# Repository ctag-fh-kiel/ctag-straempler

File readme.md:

# **CTAG Strämpler**
This repository contains the firmware and the hardwaredesigns (CTAG and [Antumbra](http://www.antumbra.eu/)) of Strämpler.

!!**NEW**!! Strämpler firmware can now be built in the cloud using Github actions
!!**NEW**!! Strämpler can now run [CTAG TBD](https://github.com/ctag-fh-kiel/ctag-tbd) as alternative firmware! Enclosed in /bin folder!

## What it is:
- Half streamer, half sampler, therefore called Strämpler (close to German word of Strampler meaning romper suit).
- Allows streaming of large audio files from SD card (limit 2GB file size due to FAT32 used).
- A eurorack modular synth module with 22 HP width and an internet connection.
- A bridge to connect to [freesound.org](https://freesound.org), to play with samples within your modular synth setup.
- Allows tweaking of your sound just like you'd do with a sampler + *a modular synth*.
- Allows to parameter tweak and modulate sounds by control voltage (CV), employing a complex modulation matrix.

## Why it is:
- A group of audio enthusiasts enjoying coding and hardware making.
- The sexiness of sampling for sound design and synthesis.
- The (subjective) need to have more sampling modules in the eurorack modular synth domain.
- The (subjective) need to make eurorack more compatible with internet of things.
- Build a platform to learn, build and practise skills, and engage students.
- To allow anyone to understand technology by offering open access.
- To benchmark the capabilities of the WiFi/BLE enabled [Espressif ESP32](https://docs.espressif.com/projects/esp-idf/en/latest/#) platform and get a deep understanding of it.
- To squeeze and optimize code so that it can work on a small embedded system.
- Because we can.
- Because of some inspiration of the [Elektron Octatrack](https://www.elektron.se/products/octatrack-mkii/).

## Features: 
- 2 voice eurorack sample streaming module.
- Streaming of large sound files from SD-card (limited by FAT32 2GB).
- Internet connection to [freesound.org](https://freesound.org), allows to download files through freesound.org api onto SD-card of module.
- One ADSR per voice to control sample amplitude.
- One band pass filter per voice with controllable base, width and Q. Can be used as low / high pass (biquad implmentation).
- Arbitrary playback speed adjustment (+/- 100%). 
- Pitching +/- 12 halftones, samples can be played e.g. using external gate / CV keyboard.
- Distortion per voice (tanh() saturation).
- Delay as send effect (stereo, ping pong, max delay time 1.5s).
- External stereo input, with delay send, mix with voices.
- Modulation matrix, where many parameters can be modulated using external CV.
- Gate and latch modes for sample playback.
- REST-API for user file upload (service discovery by MDNS / bonjour).
- 44.1kHz, 32 bit float internal resolution, 24 bit codec resolution, 12 bit CV input resolution sampled at 2KHz (yes, modulation in the audio range is possible to a certain extend), approx. 1ms DSP buffer latency  (32 words per channel).
- Approx. 100mA +12V / 10mA -12V power draw.

## Potential new features / current limitations / work to be done:
- Sampling of external input. 
- Upload to freesound.org.
- Improved sound browser, browse by tag, browse by search.
- More testing of modulation.
- More effects.
- More performance optimization.
- Automatic voice alternation.
- Bug identification and fixing.
- Code refactoring to make things more beautiful.
- More user friendly interaction.
- Documentation / tutorials.
- Your ideas?

## How to engage yourself:
- Join the [enthusiastic developer](https://codewithoutrules.com/2018/11/12/enthusiasts-vs-pragmatists/) team on Github.
- Help build and spread the hardware module (and the word).
- Use Strämpler to create cool sounds and music and share them (with a link to us).
- More ideas?

## Words of caution: 
- CTAG Strämpler does contain bugs, it comes without warranty of any kind, none of the authors are liable to damages arising by the use of it.
- CTAG Strämpler is an intermediate to advanced project, both in terms of hardware and software design:
    - In order to build the hardware you need intermediate to advanced SMD soldering skills and respective tools. I.e. the PCB contains many 0604 SMD components as well as TSSOP packages and a QFN. However, with a bit of practise you will be able to DIY build your own module. Dare and be rewarded, tackle the frustration on the path, it's worth it. The idea of the platform is also to boost your soldering skills, it *CAN* all be done by hand.
    - The software is built using [Espressif IDF](https://esp-idf.readthedocs.io) using the C programming language. Intermediate knowledge of C is required to understand the code. Furthermore, some basic DSP algorithms are applied. A DSP newbie, however, could take the project to really get rolling and build up on DSP capabilities. CTAG Strämpler is ideal to try out and play with your own DSP algorithms.
- The [Espressif ESP32](https://en.wikipedia.org/wiki/ESP32) platform used for CTAG Strämpler is, with regard to its computational power and I/O capabilities, hard at its limit. We're squeezing the platform here and are already surprised, what one can get out of $5 chip in the year 2019. Surely, other DSPs / microcontrollers could do a better job, but do they allow for internet of things as easily?

## How to get started / user manual:
See the [Wiki pages](https://github.com/ctag-fh-kiel/ctag-straempler/wiki) of this project.

## Build instructions
The easiest way is to create a fork on Github from this repository. Then make sure GitHub Actions are activated for your fork by going to the corresponding tab at your fork and clicking on the green button.
Every time you push new commits into your fork (master or dev branch) the action will build a new draft release, which will upon successful run of the action be available at your fork's release tab.

If you want to build on your own system, you can use a virtual development environment image with Docker (see here for [ESP IDF Docker instructions](https://docs.espressif.com/projects/esp-idf/en/latest/esp32/api-guides/tools/idf-docker-image.html)). 
Here are some steps:
- Install [Docker](https://www.docker.com/)
- Install [Git](https://git-scm.com/)
- Open a command line shell
- Clone the Strämpler repository and submodules with ```git clone --recurse-submodules https://github.com/ctag-fh-kiel/ctag-straempler.git``` and change into it with ```cd ctag-straempler```
- Build the firmware with ```docker run --rm -v $PWD:/project -w /project rma31/idf:v4.1-strampler idf.py build```

You can edit the source files using any IDE / text editor you like.
## Flash instructions
- Either download the firmware from the Github release tab or use your own
- Install [ESP Tool](https://github.com/espressif/esptool)
- Adapt the [Firmware flash script](https://github.com/ctag-fh-kiel/ctag-straempler/blob/master/bin/flash.sh) to your system needs and flash the firmware

## Hardware
All hardware design can be found [https://github.com/ctag-fh-kiel/esp32-eurorack-audio](https://github.com/ctag-fh-kiel/esp32-eurorack-audio).

## Links
- [Demonstration videos on YouTube](https://youtu.be/zmj8tKPHV8g).

## Licenses:
- Hardware is licensed under [Creative Commons Attribution-NonCommercial-ShareAlike 4.0 International (CC BY-NC-SA 4.0)](https://creativecommons.org/licenses/by-nc-sa/4.0/).
- Software licenses, see [license](LICENSE) file.
- Freesound license: [Freesound.org API terms](https://freesound.org/docs/api/terms_of_use.html) and [here](https://freesound.org/help/tos_api/) as well as the [freesound website terms of use](https://freesound.org/help/tos_web/).
- Don't forget to obey the license of the respective sound files used in your music. License details are shown for the individual sound file in your CTAG Strämpler sound browser, including the sound file authors name.

## Who made this happen:
- The team of [CTAG (Creative Technologies Arbeitsgruppe) at Kiel University of Applied Science](https://www.creative-technologies.de), including:
    - Robert Manzke
    - Phillip Lamp
    - Niklas Wantrupp
    - With kind support for the front panel design by David Knop from [instruments of things](http://www.instrumentsofthings.com/).
- [Antumbra](http://www.antumbra.eu/)
- More people like you :)

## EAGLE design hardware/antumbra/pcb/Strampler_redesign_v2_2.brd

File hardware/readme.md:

# Hardware
This directory contains two alternative hardware designs, the original CTAG and a beautiful smaller form factor redesign by [Antumbra](http://www.antumbra.eu/).
Apply a "git submodule update --init --recursive".

## CTAG 
Designs are in KiCad Format. Original hardware repo added through git submodule.

## Antumbra

Designs are in Eagle Cad Format.

[BOM](https://docs.google.com/spreadsheets/d/16I0Fnxrp7fq1aB0nhNF5OuEwzjhC1HZl9R4_WuAPDM4)

[Mouser cart](https://www.mouser.com/ProjectManager/ProjectDetail.aspx?AccessID=9c1a090daf)

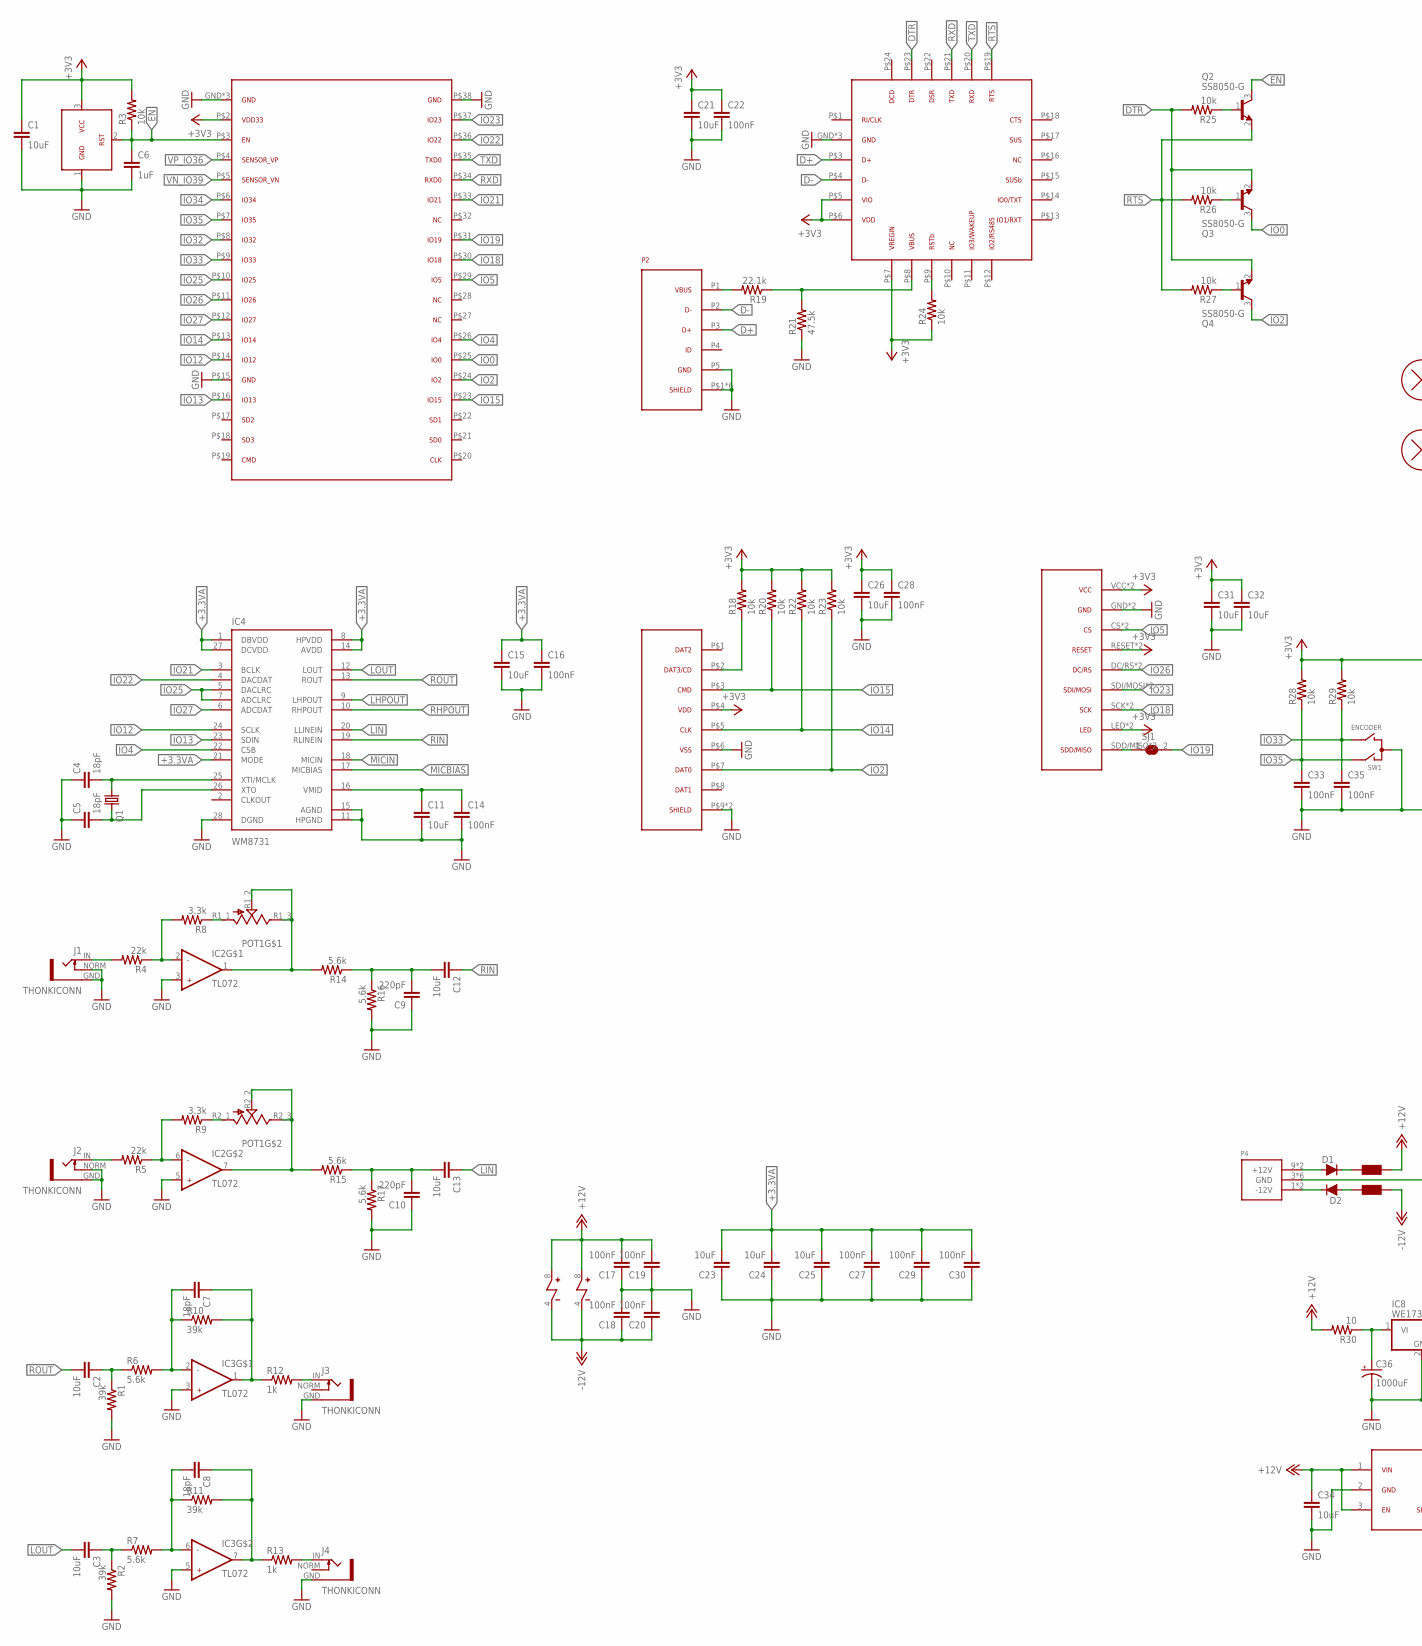
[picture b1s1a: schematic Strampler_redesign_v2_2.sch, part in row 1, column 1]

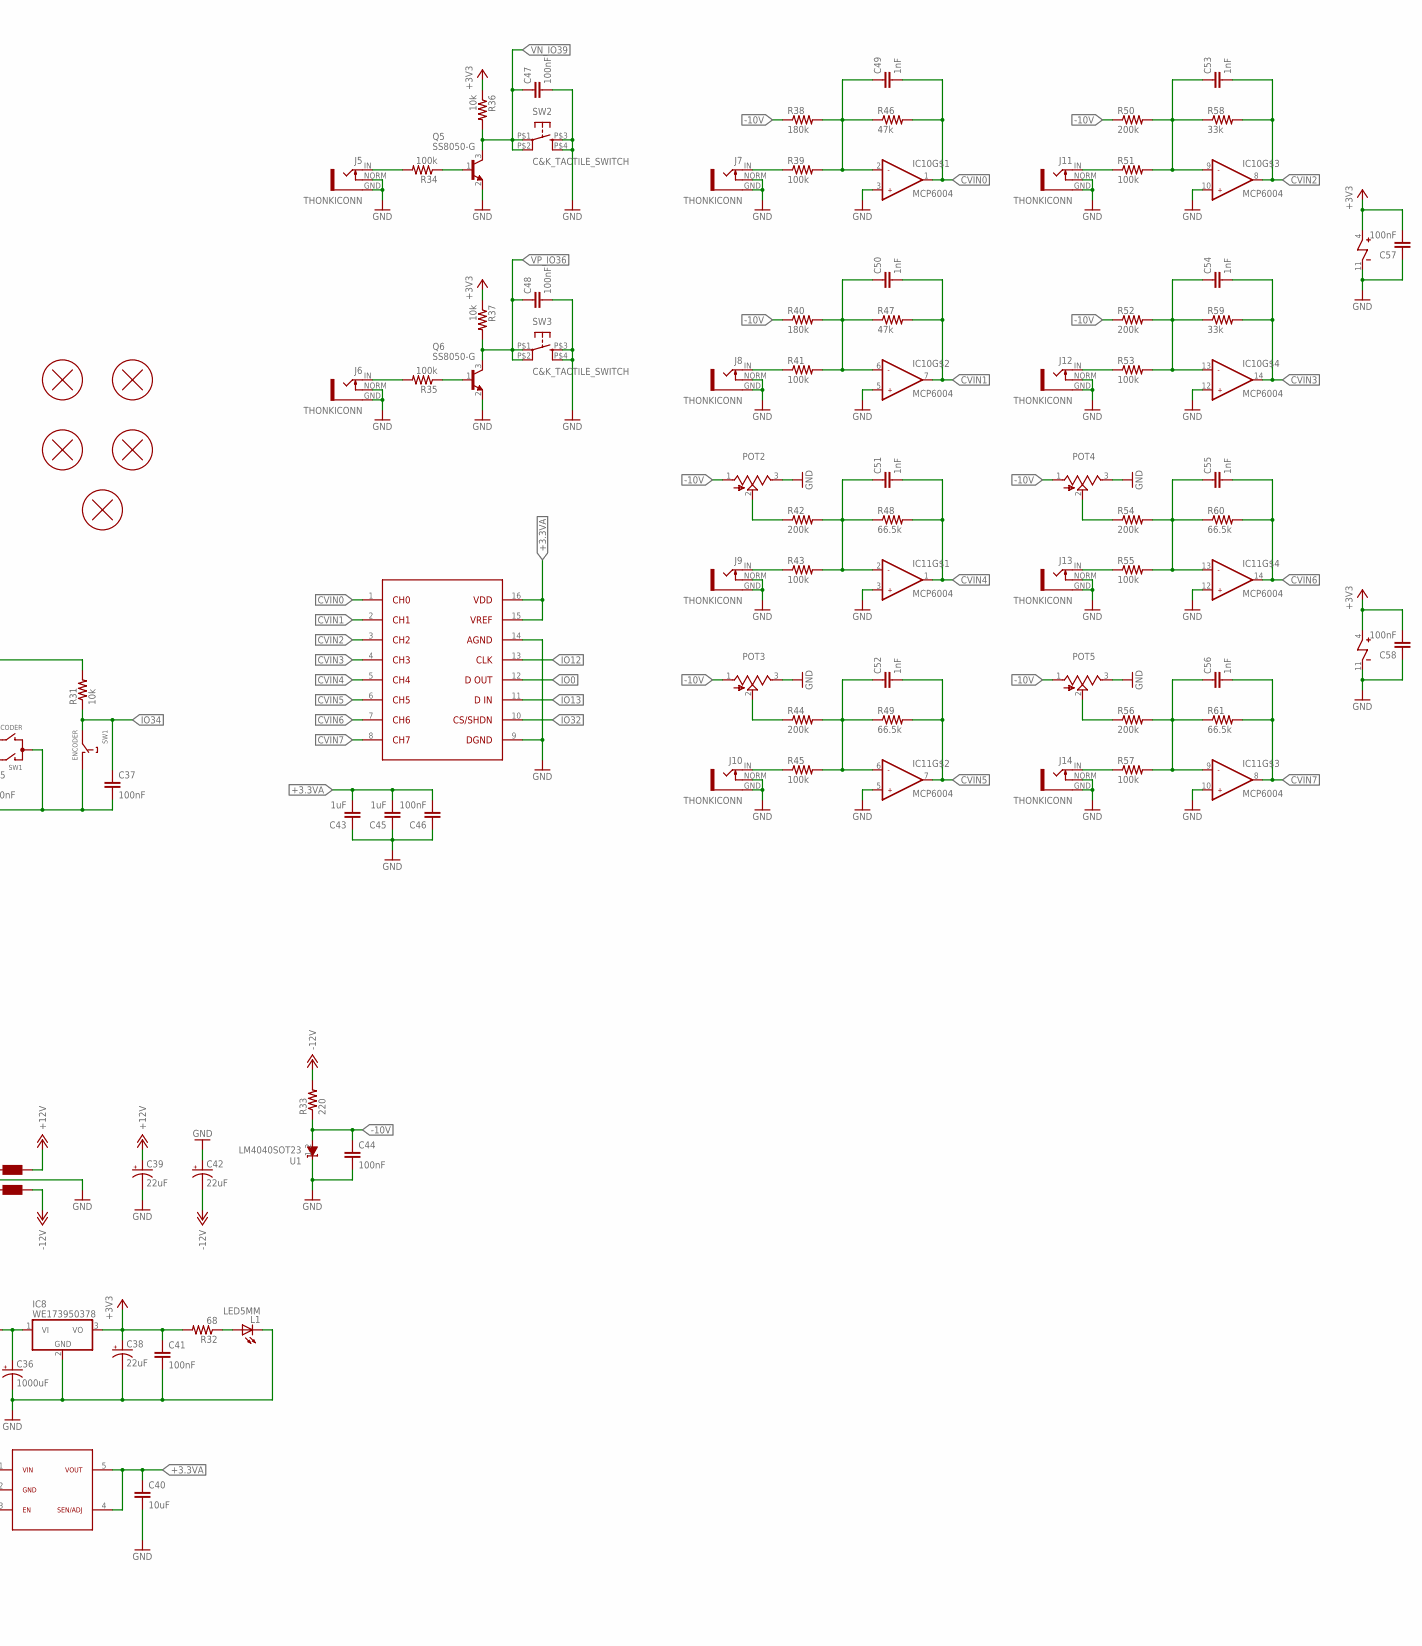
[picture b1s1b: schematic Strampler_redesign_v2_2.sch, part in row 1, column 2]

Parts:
C1, C2, C3, C11, C12, C13, C15, C21, C23, C24, C25, C26, C31, C32, C40: 10uF; R0805
C4, C5, C7, C8: 18pF; RESISTOR_0603
C6, C43, C45: 1uF; RESISTOR_0603
C9, C10: 220pF; RESISTOR_0603
C14, C16, C17, C18, C19, C20, C22, C27, C28, C29, C30, C33, C35, C37, C41, C44, C46, C47, C48, C57, C58: 100nF; RESISTOR_0603
C34: 10uF; R1210
C36: 1000uF; PANASONIC_G
C38, C39, C42: 22uF; 1206_POL
C49, C50, C51, C52, C53, C54, C55, C56: 1nF; RESISTOR_0603
D1, D2: DIODE; SOD123
F1, F2: FERRITE-BEAD0805; R0805
H1, H2, H3, H4, H5: PCB_SCREW
IC1: MIC803; SOT23
IC2, IC3: TL072; SOIC8
IC4: WM8731; SSOP28
IC5: ESP32-WROVER-B
IC6: CP2102N
IC7: ADP7118; SOT23-5L
IC8: WE173950378; WE78
IC9: MCP3208; SOIC16
IC10, IC11: MCP6004; TSSOP14
J1, J2, J3, J4, J5, J6, J7, J8, J9, J10, J11, J12, J13, J14: THONKICONN; PROTOJACK
L1: LED5MM; LED_5MM
P1: SD-CARD; SD-CARD-THONK
P2: USB-B; USB-B-MOLEX-1050170001
P3: MSP2202_DISPLAY
P4: POWER_SIMPLE10; POWER_10
POT1: POT_DUAL_THONK
POT2, POT3, POT4, POT5: POT_VERTICAL; ALPS_POT_VERTICAL
Q1: CRYSTAL; HC49UP
Q2, Q3, Q4, Q5, Q6: SS8050-G; SOT23
R1, R2, R10, R11: 39k; RESISTOR_0603
R3, R18, R20, R22, R23, R24, R25, R26, R27, R28, R29, R31, R36, R37: 10k; RESISTOR_0603
R4, R5: 22k; RESISTOR_0603
R6, R7, R14, R15, R16, R17: 5.6k; RESISTOR_0603
R8, R9: 3.3k; RESISTOR_0603
R12, R13: 1k; RESISTOR_0603
R19: 22.1k; RESISTOR_0603
R21: 47.5k; RESISTOR_0603
R30: 10; R2512
R32: 68; RESISTOR_0603
R33: 220; RESISTOR_0603
R34, R35, R39, R41, R43, R45, R51, R53, R55, R57: 100k; RESISTOR_0603
R38, R40: 180k; RESISTOR_0603
R42, R44, R50, R52, R54, R56: 200k; RESISTOR_0603
R46, R47: 47k; RESISTOR_0603
R48, R49, R60, R61: 66.5k; RESISTOR_0603
R58, R59: 33k; RESISTOR_0603
SJ1: SJ
SW1: ENCODER; ALPS_EC12E_SW
SW2, SW3: C&K_TACTILE_SWITCH
U1: LM4040SOT23; SOT23

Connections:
+3.3VA: C15.1, C16.1, C23.2, C24.2, C25.2, C27.2, C29.2, C30.2, C40.1, C43.2, C45.2, C46.2, IC4.1 (DBVDD), IC4.8 (HPVDD), IC4.14 (AVDD), IC4.21 (MODE), IC4.27 (DCVDD), IC7.4, IC7.5, IC9.15, IC9.16
+3V3: C1.1, C21.1, C22.1, C26.1, C28.1, C31.1, C32.1, C38.2 (+), C41.1, C57.2, C58.2, IC1.3, IC5.P$2, IC6.P$5, IC6.P$6, IC6.P$7, IC8.3 (VO), IC10.4, IC11.4, P1.P$4, P3.LED, P3.LED1, P3.RESET, P3.RESET1, P3.VCC, P3.VCC1, R3.2, R18.2, R20.2, R22.2, R23.2, R24.1, R28.2, R29.2, R31.2, R32.2, R36.1, R37.1
+12V: C17.2, C19.2, C34.1, C39.2 (+), F1.1, IC2.8, IC3.8, IC7.1, IC7.3, R30.2
-10V: C44.1, POT2.1 (A), POT3.1 (A), POT4.1 (A), POT5.1 (A), R33.1, R38.1, R40.1, R50.1, R52.1, U1.2 (A)
-12V: C18.1, C20.1, C42.1 (-), F2.1, IC2.4, IC3.4, R33.2
CVIN0: C49.2, IC9.1, IC10.1, R46.2
CVIN1: C50.2, IC9.2, IC10.7, R47.2
CVIN2: C53.2, IC9.3, IC10.8, R58.2
CVIN3: C54.2, IC9.4, IC10.14, R59.2
CVIN4: C51.2, IC9.5, IC11.1, R48.2
CVIN5: C52.2, IC9.6, IC11.7, R49.2
CVIN6: C55.2, IC9.7, IC11.14, R60.2
CVIN7: C56.2, IC9.8, IC11.8, R61.2
D+: IC6.P$3, P2.P3
D-: IC6.P$4, P2.P2
DTR: IC6.P$23, Q3.2 (E), Q4.2 (E), R25.2
EN: C6.1, IC1.2, IC5.P$3, Q2.3 (C), R3.1
GND: C1.2, C4.1, C5.1, C6.2, C9.1, C10.1, C11.2, C14.2, C15.2, C16.2, C17.1, C18.2, C19.1, C20.2, C21.2, C22.2, C23.1, C24.1, C25.1, C26.2, C27.1, C28.2, C29.1, C30.1, C31.2, C32.2, C33.2, C34.2, C35.2, C36.-, C37.2, C38.1 (-), C39.1 (-), C40.2, C41.2, C42.2 (+), C43.1, C44.2, C45.1, C46.1, C47.2, C48.2, C57.1, C58.1, IC1.1, IC2.3, IC2.5, IC3.3, IC3.5, IC4.11 (HPGND), IC4.15 (AGND), IC4.28 (DGND), IC5.GND, IC5.GND2, IC5.P$1, IC5.P$15, IC5.P$38, IC6.GND, IC6.GND2, IC6.P$2, IC7.2, IC8.2 (GND), IC9.9, IC9.14, IC10.3, IC10.5, IC10.10, IC10.11, IC10.12, IC11.3, IC11.5, IC11.10, IC11.11, IC11.12, J1.GND, J1.NORM, J2.GND, J2.NORM, J3.GND, J4.GND, J5.GND, J5.NORM, J6.GND, J6.NORM, J7.GND, J7.NORM, J8.GND, J8.NORM, J9.GND, J9.NORM, J10.GND, J10.NORM, J11.GND, J11.NORM, J12.GND, J12.NORM, J13.GND, J13.NORM, J14.GND, J14.NORM, L1.K (C), P1.P$6, P1.P$9, P1.P$10, P2.P5, P2.P$1, P2.P$2, P2.P$8, P2.P$9, P2.P$10, P2.P$11, P3.GND, P3.GND1, P4.3 (GND), P4.4 (GND), P4.5 (GND), P4.6 (GND), P4.7 (GND), P4.8 (GND), POT2.3 (B), POT3.3 (B), POT4.3 (B), POT5.3 (B), Q5.2 (E), Q6.2 (E), R1.2, R2.2, R16.2, R17.2, R21.1, SW1.C, SW1.D (1), SW2.P$3 (3), SW2.P$4 (4), SW3.P$3 (3), SW3.P$4 (4), U1.1 (C)
IO0: IC5.P$25, IC9.12, Q3.3 (C)
IO2: IC5.P$24, P1.P$7, Q4.3 (C), R23.1
IO4: IC4.22 (CSB), IC5.P$26
IO5: IC5.P$29, P3.CS, P3.CS1
IO12: IC4.24 (SCLK), IC5.P$14, IC9.13
IO13: IC4.23 (SDIN), IC5.P$16, IC9.11
IO14: IC5.P$13, P1.P$5, R22.1
IO15: IC5.P$23, P1.P$3, R20.1
IO18: IC5.P$30, P3.SCK, P3.SCK1
IO19: IC5.P$31, SJ1.2
IO21: IC4.3 (BCLK), IC5.P$33
IO22: IC4.4 (DACDAT), IC5.P$36
IO23: IC5.P$37, P3.SDI/MOSI, P3.SDI/MOSI1
IO25: IC4.5 (DACLRC), IC4.7 (ADCLRC), IC5.P$10
IO26: IC5.P$11, P3.DC/RS, P3.DC/RS1
IO27: IC4.6 (ADCDAT), IC5.P$12
IO32: IC5.P$8, IC9.10
IO33: C35.1, IC5.P$9, R29.1, SW1.B
IO34: C37.1, IC5.P$6, R31.1, SW1.E (2)
IO35: C33.1, IC5.P$7, R28.1, SW1.A
LHPOUT: IC4.9 (LHPOUT)
LIN: C13.1, IC4.20 (LLINEIN)
LOUT: C3.2, IC4.12 (LOUT)
MICBIAS: IC4.17 (MICBIAS)
MICIN: IC4.18 (MICIN)
unnamed: IC6.P$9, R24.2
unnamed: IC6.P$8, R19.1, R21.2
unnamed: Q2.1 (B), R25.1
unnamed: P2.P1, R19.2
unnamed: P1.P$2, R18.1
unnamed: Q3.1 (B), R26.1
unnamed: P3.SDD/MISO, P3.SDD/MISO1, SJ1.1
unnamed: J5.IN, R34.2
unnamed: Q4.1 (B), R27.1
unnamed: J6.IN, R35.2
unnamed: Q5.1 (B), R34.1
unnamed: Q6.1 (B), R35.1
unnamed: J7.IN, R39.1
unnamed: J11.IN, R51.1
unnamed: C53.1, IC10.9, R50.2, R51.2, R58.1
unnamed: J8.IN, R41.1
unnamed: C49.1, IC10.2, R38.2, R39.2, R46.1
unnamed: POT3.2 (W), R44.1
unnamed: C50.1, IC10.6, R40.2, R41.2, R47.1
unnamed: J12.IN, R53.1
unnamed: C54.1, IC10.13, R52.2, R53.2, R59.1
unnamed: POT2.2 (W), R42.1
unnamed: J9.IN, R43.1
unnamed: C51.1, IC11.2, R42.2, R43.2, R48.1
unnamed: J13.IN, R55.1
unnamed: C55.1, IC11.13, R54.2, R55.2, R60.1
unnamed: J10.IN, R45.1
unnamed: C52.1, IC11.6, R44.2, R45.2, R49.1
unnamed: J14.IN, R57.1
unnamed: C56.1, IC11.9, R56.2, R57.2, R61.1
unnamed: J1.IN, R4.2
unnamed: IC2.2, R4.1, R8.2
unnamed: D1.+, P4.9 (+12V), P4.10 (+12V)
unnamed: POT1.R1_1 (A), R8.1
unnamed: POT5.2 (W), R56.1
unnamed: IC2.1, POT1.R1_2 (W), POT1.R1_3 (B), R14.2
unnamed: C9.2, C12.2, R14.1, R16.1
unnamed: POT4.2 (W), R54.1
unnamed: J2.IN, R5.2
unnamed: IC2.6, R5.1, R9.2
unnamed: POT1.R2_1 (A), R9.1
unnamed: IC2.7, POT1.R2_2 (W), POT1.R2_3 (B), R15.2
unnamed: C5.2, IC4.26 (XTO), Q1.2
unnamed: C4.2, IC4.25 (XTI/MCLK), Q1.1
unnamed: C10.2, C13.2, R15.1, R17.1
unnamed: C7.1, IC3.1, R10.2, R12.1
unnamed: D1.-, F1.2
unnamed: C7.2, IC3.2, R6.2, R10.1
unnamed: C2.1, R1.1, R6.1
unnamed: C36.+, IC8.1 (VI), R30.1
unnamed: J3.IN, R12.2
unnamed: D2.-, P4.1 (-12V), P4.2 (-12V)
unnamed: C8.1, IC3.7, R11.2, R13.1
unnamed: C8.2, IC3.6, R7.2, R11.1
unnamed: C11.1, C14.1, IC4.16 (VMID)
unnamed: C3.1, R2.1, R7.1
unnamed: J4.IN, R13.2
unnamed: D2.+, F2.2
unnamed: L1.A, R32.1
RHPOUT: IC4.10 (RHPOUT)
RIN: C12.1, IC4.19 (RLINEIN)
ROUT: C2.2, IC4.13 (ROUT)
RTS: IC6.P$19, Q2.2 (E), R26.2, R27.2
RXD: IC5.P$34, IC6.P$21
TXD: IC5.P$35, IC6.P$20
VN_IO39: C47.1, IC5.P$5, Q5.3 (C), R36.2, SW2.P$1 (1), SW2.P$2 (2)
VP_IO36: C48.1, IC5.P$4, Q6.3 (C), R37.2, SW3.P$1 (1), SW3.P$2 (2)

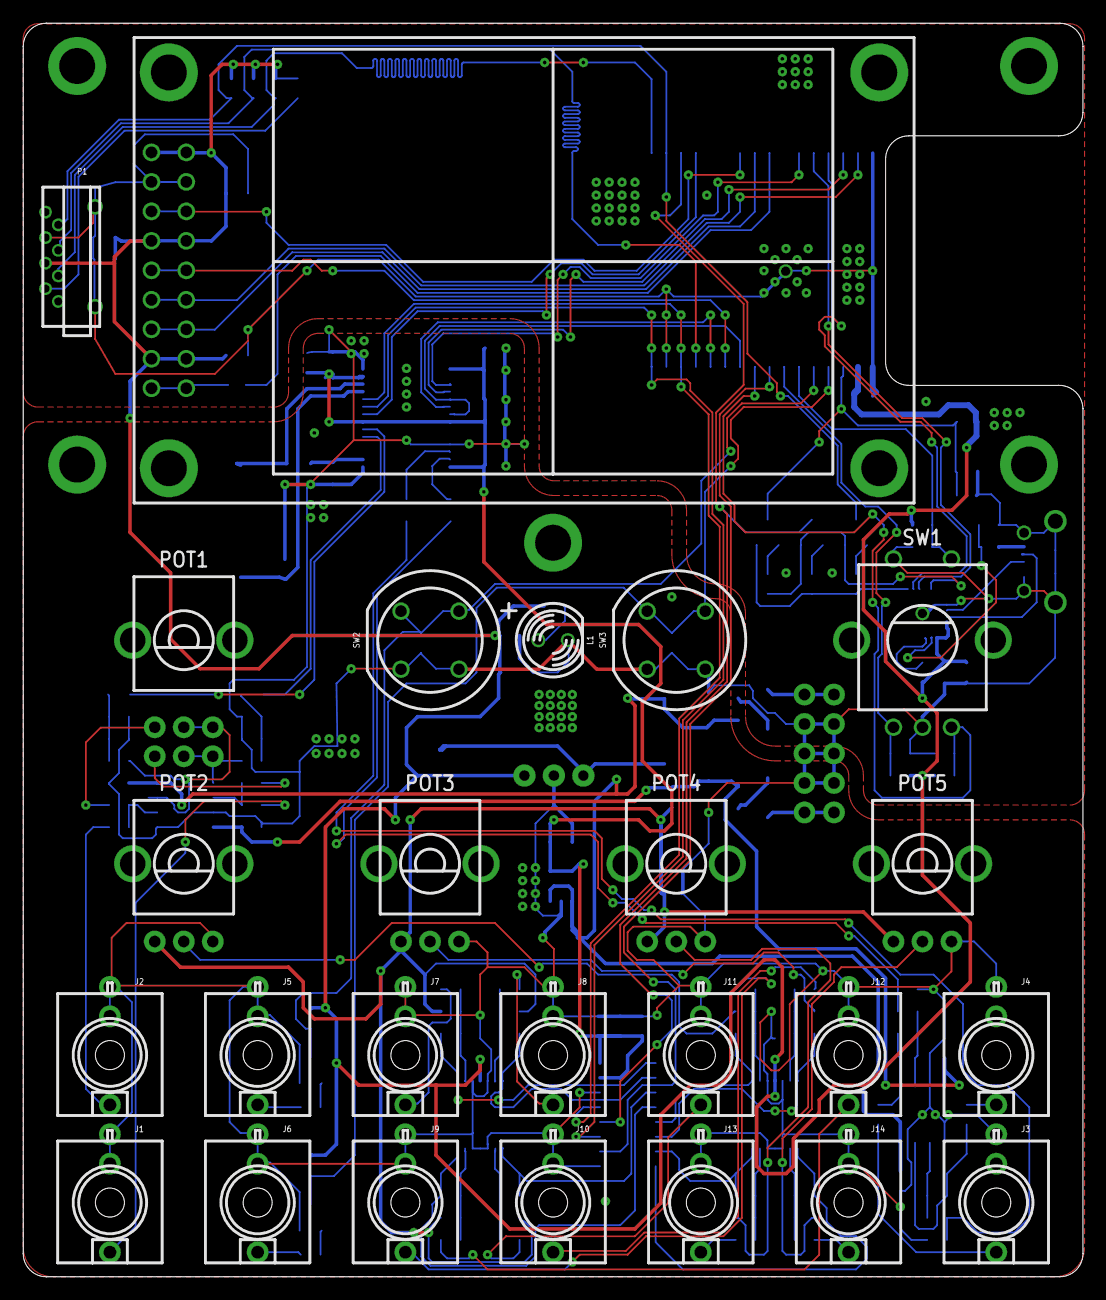
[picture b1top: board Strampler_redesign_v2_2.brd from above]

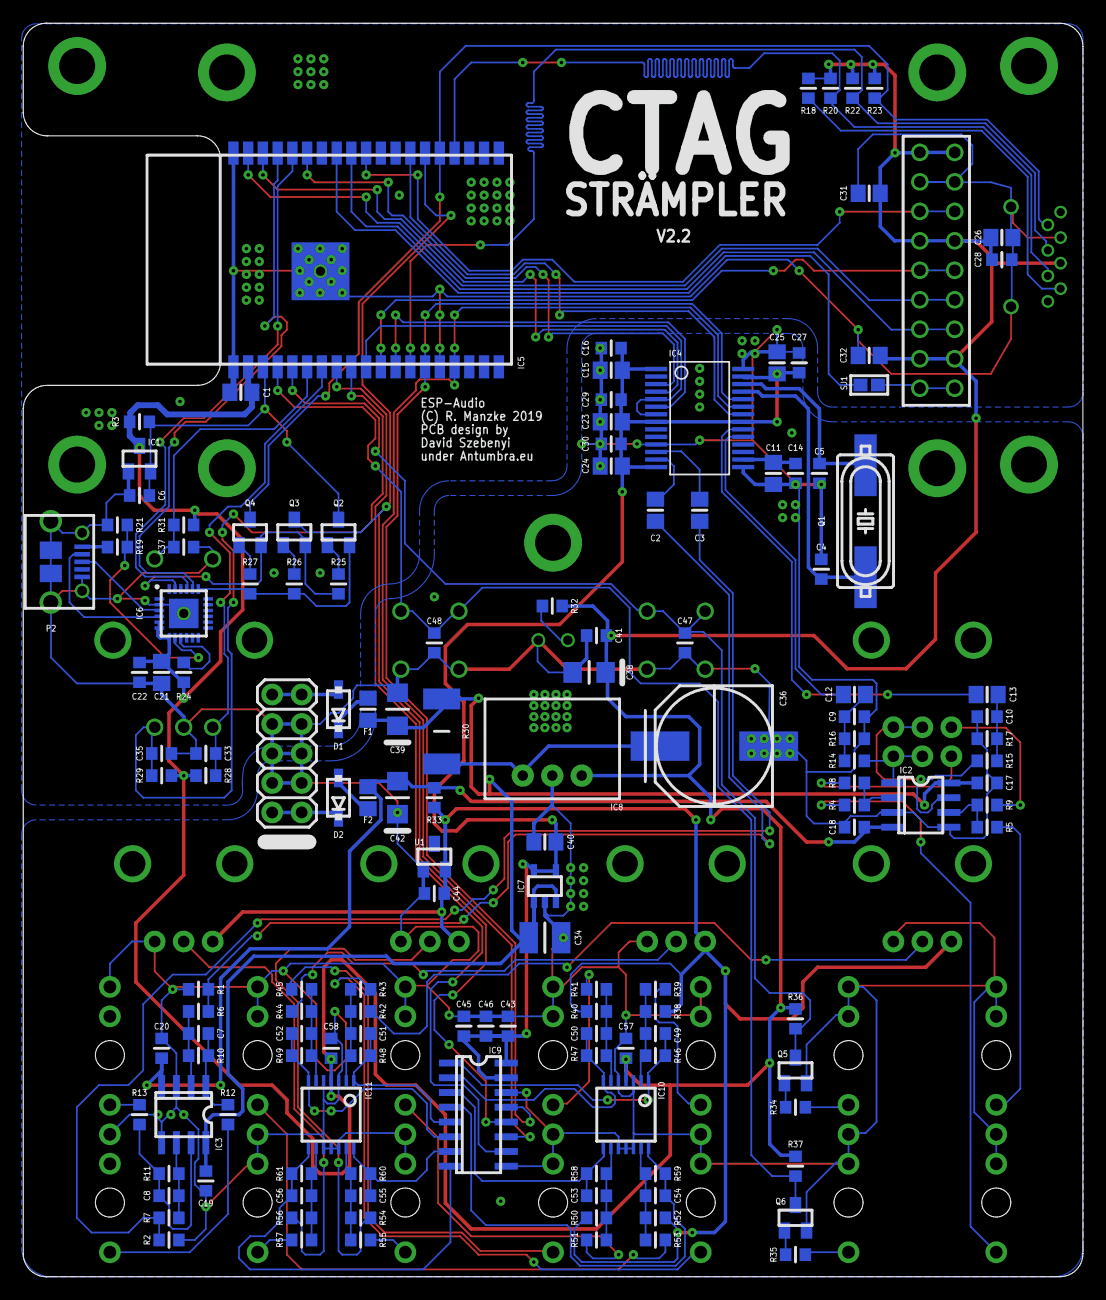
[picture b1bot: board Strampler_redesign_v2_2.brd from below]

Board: 2 copper layers, 91.3 x 108.0 mm, 174 parts (144 on the bottom side), 106 nets.

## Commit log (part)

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2019-04-27 initial
2019-04-27 sdkconfig added
2019-04-27 link updated
2019-04-27 links updated
2019-04-27 image added
2019-05-02 improved input-menu character spacing
2019-05-04 added config file validation at device start
2019-05-05 binary files of app added, including script for flashing
2019-05-06 when swapping a sample sample start, loop start and loop end get updated correctly
2019-05-06 new idf
2019-06-14 issue Playback partially corrupted when start + PBspeed modulated
2019-06-15 audio file structure repair method
2019-06-16 silence file for initial slot assignment implemented
2019-06-17 modified menusys -> enabling menu transitions from initial menu, fixed crash when trying to select sound if pool is emtpy
2019-06-17 disabling tag browsing for the moment, as it's not fully implemented
2019-06-17 binaries updated, after stability fixes
2019-06-23 working on freesound file not found
2019-06-23 freesound file not found, fixes crash
2019-06-23 updated bins
2019-06-23 sample menu only enabled when connected to WiFi
2019-07-21 API key input fixed
2020-02-24 changed SPI flash speed to 40MHz
2020-02-25 increased stack size
2021-02-07 straempler tbd alternative fw
2021-03-15 hardware added, Antumbra designs added
2021-03-15 typo corrected
2021-03-15 more readme, updated flash script
2021-03-15 antumbra image
2021-09-02 towards idf migration
2021-09-02 compiles now with idf 4.1
2021-09-02 github action, esp idf patch
2021-09-03 removed symlinks
2021-09-03 remove esp-request
2021-09-03 cleanups + defaults
2021-09-03 strange issue with mp3 decoding task
2021-09-03 rename defaults
2021-09-03 first working with idf 4.1
2021-09-03 strampler idf in docker image
2021-09-03 idf_4_1 + freesound https api working binaries
2021-09-04 removed CMake-based IDF change
2021-09-11 fixed build warnings
2021-09-11 progress calculation modified
2021-09-11 v0.9 release fw
2022-07-08 Update readme.md
    --recurse-submodules
